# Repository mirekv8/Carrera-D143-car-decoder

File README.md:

# Carrera D143 Car Decoder
Customized firmware for the Carrera Digital 143 decoder. The base is firmware from https://github.com/azya52/carrera. All functions work with CU 30352. 
Other features: 
-  Setting from CU 30352
-  Ghost car function
-  Front light support.
-  Break light support
-  Five custom speed curves are stored in EEPROM

  :100000000004000000FFFFFFFFFFFFFFFFFFFFFFF7<br/>
  :1000100000050A14191E23282D32373C46505A6E0B<br/>
  :10002000000A141F29333D47525C66707C858F9906<br/>
  :1000300000262E38414D555E67727C858E97A1B3A0<br/>
  :1000400000112233445566778899AABBCCDDEEFFB8<br/>
  :1000500000020D18232E39444F5A697D96AFD2FF06<br/>
  :10006000FFFFFFFFFFFFFFFFFFFFFFFFFFFFFFFFA0<br/>
  :10007000FFFFFFFFFFFFFFFFFFFFFFFF1004005325<br/>
  :00000001FF<br/>

-  A calibration value must be stored at 0x7f

# Calibration
A lot depends on calibration. I use https://github.com/felias-fogg/avrCalibrate for calibration. They set a calibration value of 1200000 not 1000000.

# Wiring

# Speed curves

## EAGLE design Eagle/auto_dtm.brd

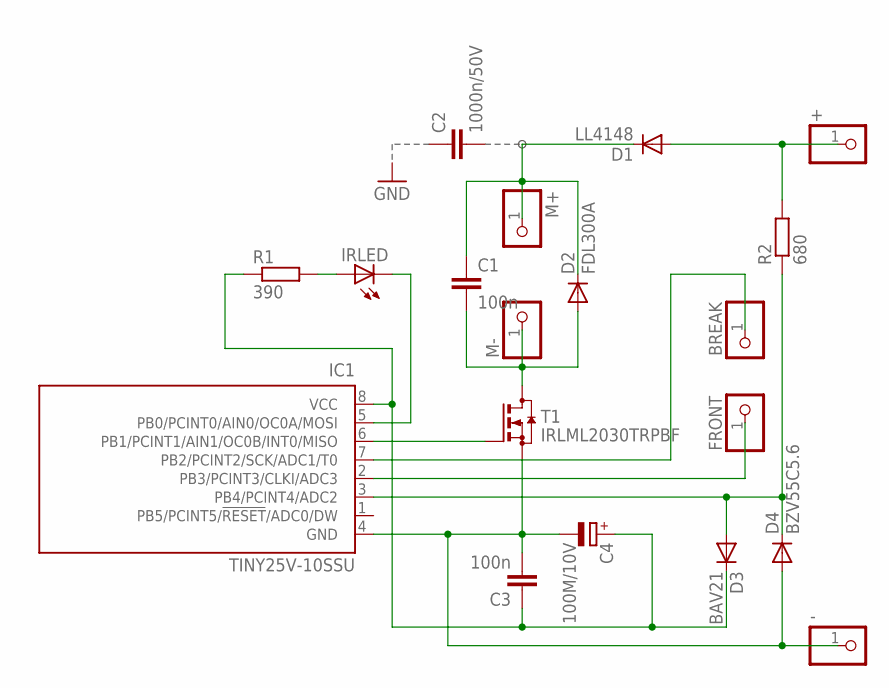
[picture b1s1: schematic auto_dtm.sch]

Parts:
+: PINHD-1X1; 1X01
-: PINHD-1X1; 1X01
BREAK: PINHD-1X1; 1X01
C1, C3: 100n; C1206
C2: 1000n/50V; C025-024X044
C4: 100M/10V; SMC_C
D1: LL4148; MINIMELF
D2: FDL300A; MINIMELF
D3: BAV21; MINIMELF
D4: BZV55C5.6; MINIMELF
FRONT: PINHD-1X1; 1X01
IC1: TINY25V-10SSU; 8S1
IRLED: LED3MM
M+: PINHD-1X1; 1X01
M-: PINHD-1X1; 1X01
R1: 390; R1206
R2: 680; R1206
T1: IRLML2030TRPBF; SOT23

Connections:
GND: -.1, C3.2, C4.-, D4.A, IC1.4 (GND), T1.2 (S)
unnamed: IC1.6 (PB1/PCINT1/AIN1/OC0B/INT0/MISO), T1.1 (G)
unnamed: C1.2, D2.A, M-.1, T1.3 (D)
unnamed: C1.1, D1.C, D2.C, M+.1
unnamed: IC1.5 (PB0/PCINT0/AIN0/OC0A/MOSI), IRLED.K (C)
unnamed: +.1, D1.A, R2.2
unnamed: IRLED.A, R1.2
unnamed: D3.A, D4.C, IC1.3 (PB4/PCINT4/ADC2), R2.1
unnamed: FRONT.1, IC1.2 (PB3/PCINT3/CLKI/ADC3)
unnamed: BREAK.1, IC1.7 (PB2/PCINT2/SCK/ADC1/T0)
VCC: C3.1, C4.+, D3.C, IC1.8 (VCC), R1.1

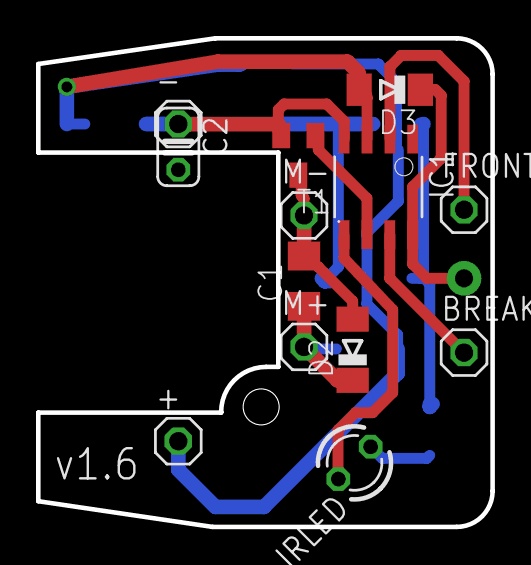
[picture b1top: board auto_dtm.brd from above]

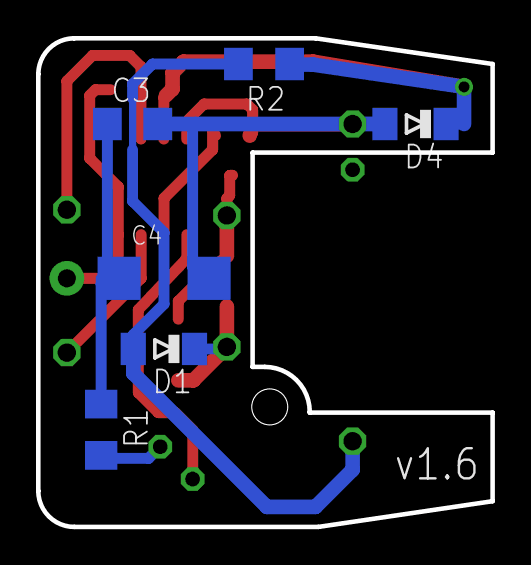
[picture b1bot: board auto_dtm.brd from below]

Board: 2 copper layers, 25.2 x 27.1 mm, 19 parts (6 on the bottom side), 11 nets.

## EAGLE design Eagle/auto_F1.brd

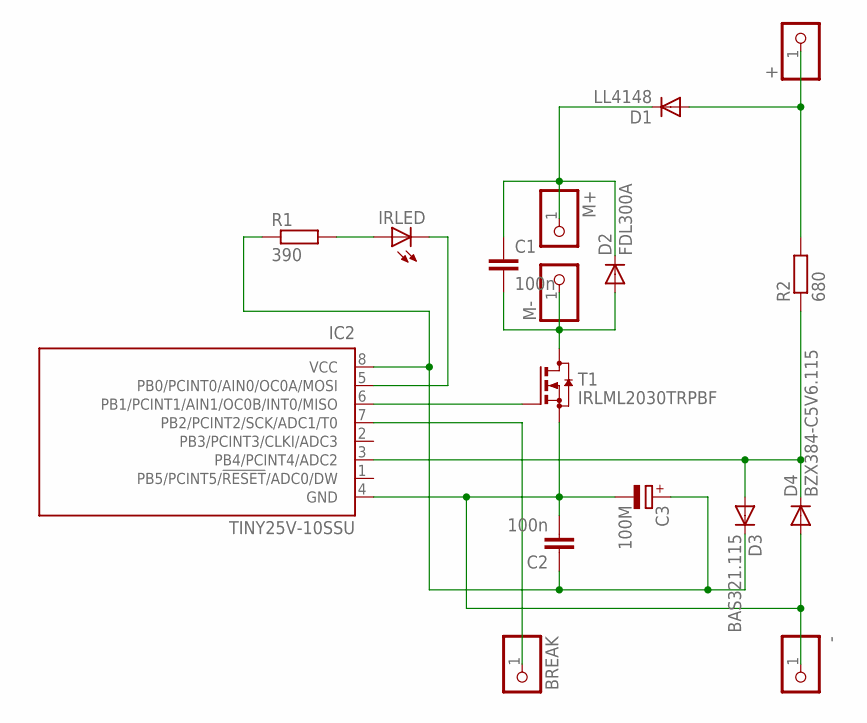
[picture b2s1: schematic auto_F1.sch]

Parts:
+: PINHD-1X1; 1X01
-: PINHD-1X1; 1X01
BREAK: PINHD-1X1; 1X01
C1, C2: 100n; C1206
C3: 100M; SMC_C
D1: LL4148; MINIMELF
D2: FDL300A; MINIMELF
D3: BAS321.115; MICROMELF-W
D4: BZX384-C5V6.115; MICROMELF-W
IC2: TINY25V-10SSU; 8S1
IRLED: LED3MM
M+: PINHD-1X1; 1X01
M-: PINHD-1X1; 1X01
R1: 390; R1206
R2: 680; R1206
T1: IRLML2030TRPBF; SOT23

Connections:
GND: -.1, C2.2, C3.-, D4.A, IC2.4 (GND), T1.2 (S)
unnamed: IC2.6 (PB1/PCINT1/AIN1/OC0B/INT0/MISO), T1.1 (G)
unnamed: C1.2, D2.A, M-.1, T1.3 (D)
unnamed: C1.1, D1.C, D2.C, M+.1
unnamed: IC2.5 (PB0/PCINT0/AIN0/OC0A/MOSI), IRLED.K (C)
unnamed: +.1, D1.A, R2.2
unnamed: IRLED.A, R1.2
unnamed: D3.A, D4.C, IC2.3 (PB4/PCINT4/ADC2), R2.1
unnamed: BREAK.1, IC2.7 (PB2/PCINT2/SCK/ADC1/T0)
VCC: C2.1, C3.+, D3.C, IC2.8 (VCC), R1.1

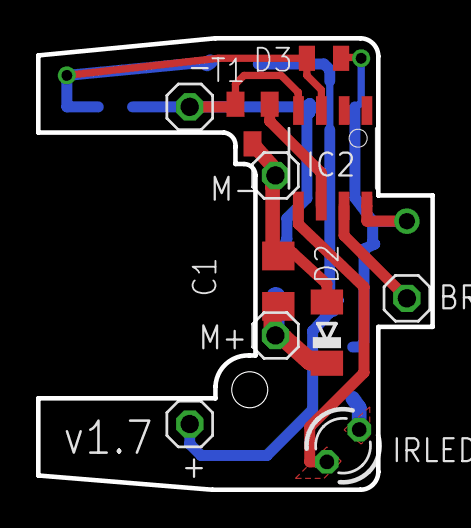
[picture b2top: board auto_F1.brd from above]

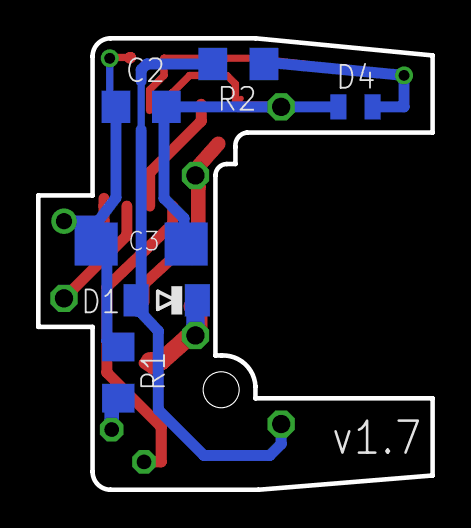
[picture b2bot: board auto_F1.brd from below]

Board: 2 copper layers, 21.9 x 25.1 mm, 17 parts (6 on the bottom side), 10 nets.

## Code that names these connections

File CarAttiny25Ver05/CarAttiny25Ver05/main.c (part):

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#include <avr/power.h>
#include <avr/pgmspace.h>

#define TRACK_PIN PB4
#define MOTOR_PIN PB1
#define IRLED_PIN PB0
#define FRONTLIGHT_PIN PB3
#define STOPLIGHT_PIN PB2
#define NU_PIN3 PB5

#define PACKET_PERIOD_MS 75
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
